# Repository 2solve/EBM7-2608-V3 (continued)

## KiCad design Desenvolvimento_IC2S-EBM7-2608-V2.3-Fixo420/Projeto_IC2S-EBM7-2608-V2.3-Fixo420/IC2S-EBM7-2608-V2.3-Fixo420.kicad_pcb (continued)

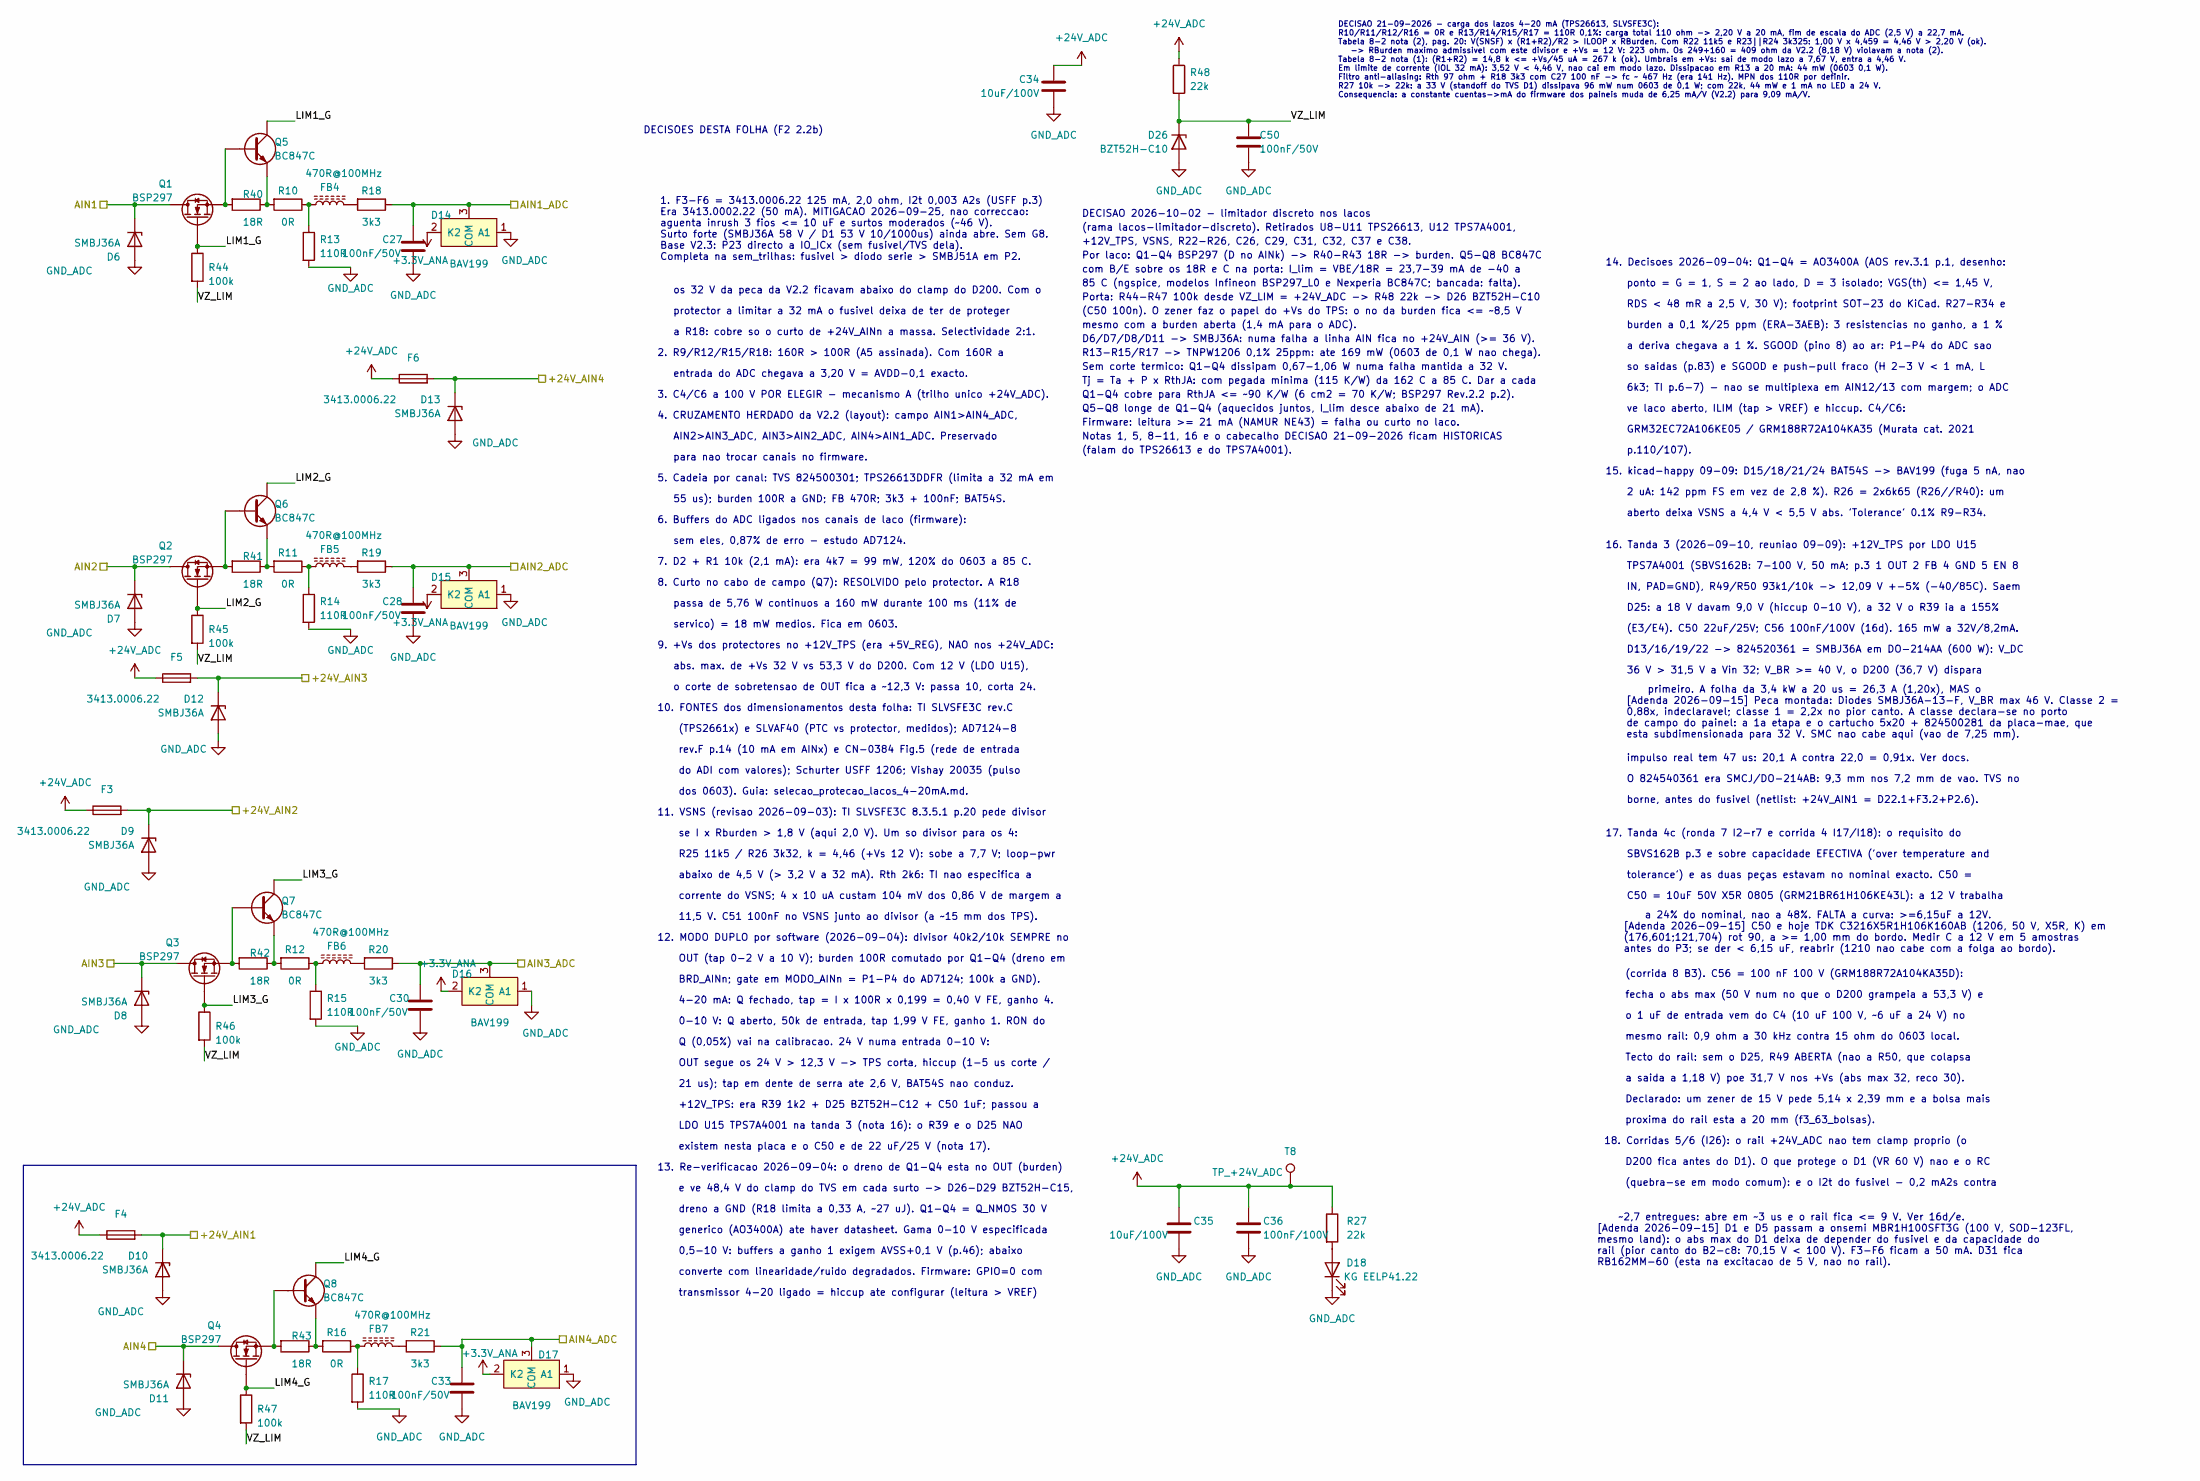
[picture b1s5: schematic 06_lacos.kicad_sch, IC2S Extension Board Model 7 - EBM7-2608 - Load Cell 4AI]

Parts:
C27, C28, C30, C33, C50: 100nF/50V; 0603C; MPN C1608X7R1H104K080AA
C34, C35: 10uF/100V; C_1210_3225Metric; MPN GRM32EC72A106ME05L
C36: 100nF/100V; 0603C; MPN GRM188R72A104KA35D
D6, D7, D8, D9, D10, D11, D12, D13: SMBJ36A; DO-214AA; MPN SMBJ36A-13-F
D14, D15, D16, D17: BAV199; SOT23-3; MPN BAV199LT1G
D18: KG EELP41.22; 0603LED; MPN KG EELP41.22-PHRH-35-A8J8-20-R18
D26: BZT52H-C10; SOD-123F; MPN BZT52H-C10,115
F3, F4, F5, F6: 3413.0006.22; 1206F; MPN 3413.0006.22
FB4, FB5, FB6, FB7: 470R@100MHz; 0603FB; MPN BLM18PG471SN1D
Q1, Q2, Q3, Q4: BSP297; SOT-223-3_TabPin2; MPN BSP297H6327XTSA1
Q5, Q6, Q7, Q8: BC847C; SOT-23; MPN BC847C,215
R10, R11, R12, R16: 0R; 0603R; Tolerance 0.1%; MPN RC0603JR-070RL
R13, R14, R15, R17: 110R; 1206R; Tolerance 0.1%; MPN TNPW1206110RBEEA
R18, R19, R20, R21: 3k3; 0603R; MPN RC0603FR-073K3L
R27: 22k; 0603R; MPN ERJ-3EKF2202V
R40, R41, R42, R43: 18R; 0603R; Tolerance 1%; MPN RC0603FR-0718RL
R44, R45, R46, R47: 100k; 0603R; Tolerance 1%; MPN RC0603FR-07100KL
R48: 22k; 0603R; Tolerance 1%; MPN RC0603FR-0722KL
T8: TP_+24V_ADC; TestPad_Via

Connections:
+3.3V_ANA: D14.2 (K2), D15.2 (K2), D16.2 (K2), D17.2 (K2); also elsewhere on the board
+24V_ADC: C34.1, C35.1, C36.1, F3.1, F4.1, F5.1, F6.1, R27.1, R48.1, T8.1 (1_1); also elsewhere on the board
/1 Conectores/+24V_AIN1: D10.1 (K), F4.2; also elsewhere on the board
/1 Conectores/+24V_AIN2: D9.1 (K), F3.2; also elsewhere on the board
/1 Conectores/+24V_AIN3: D12.1 (K), F5.2; also elsewhere on the board
/1 Conectores/+24V_AIN4: D13.1 (K), F6.2; also elsewhere on the board
/1 Conectores/AIN1: D6.1 (K), Q1.2 (D); also elsewhere on the board
/1 Conectores/AIN2: D7.1 (K), Q2.2 (D); also elsewhere on the board
/1 Conectores/AIN3: D8.1 (K), Q3.2 (D); also elsewhere on the board
/1 Conectores/AIN4: D11.1 (K), Q4.2 (D); also elsewhere on the board
/5 ADC/AIN1_ADC: C27.2, D14.3 (COM), R18.1; also elsewhere on the board
/5 ADC/AIN2_ADC: C28.2, D15.3 (COM), R19.1; also elsewhere on the board
/5 ADC/AIN3_ADC: C30.2, D16.3 (COM), R20.1; also elsewhere on the board
/5 ADC/AIN4_ADC: C33.2, D17.3 (COM), R21.1; also elsewhere on the board
/6 Lacos 4-20mA/LIM1_G: Q1.1 (G), Q5.3 (C), R44.1
/6 Lacos 4-20mA/LIM2_G: Q2.1 (G), Q6.3 (C), R45.1
/6 Lacos 4-20mA/LIM3_G: Q3.1 (G), Q7.3 (C), R46.1
/6 Lacos 4-20mA/LIM4_G: Q4.1 (G), Q8.3 (C), R47.1
/6 Lacos 4-20mA/VZ_LIM: C50.1, D26.1 (K), R44.2, R45.2, R46.2, R47.2, R48.2
GND_ADC: C27.1, C28.1, C30.1, C33.1, C34.2, C35.2, C36.2, C50.2, D6.2 (A), D7.2 (A), D8.2 (A), D9.2 (A), D10.2 (A), D11.2 (A), D12.2 (A), D13.2 (A), D14.1 (A1), D15.1 (A1), D16.1 (A1), D17.1 (A1), D18.1 (K), D26.2 (A), R13.2, R14.2, R15.2, R17.2; also elsewhere on the board
unnamed: D18.2 (A), R27.2
unnamed: FB4.1, R10.1, R13.1
unnamed: FB4.2, R18.2
unnamed: FB5.1, R11.1, R14.1
unnamed: FB5.2, R19.2
unnamed: FB6.1, R12.1, R15.1
unnamed: FB6.2, R20.2
unnamed: FB7.1, R16.1, R17.1
unnamed: FB7.2, R21.2
unnamed: Q1.3 (S), Q5.1 (B), R40.2
unnamed: Q2.3 (S), Q6.1 (B), R41.2
unnamed: Q3.3 (S), Q7.1 (B), R42.2
unnamed: Q4.3 (S), Q8.1 (B), R43.2
unnamed: Q5.2 (E), R10.2, R40.1
unnamed: Q6.2 (E), R11.2, R41.1
unnamed: Q7.2 (E), R12.2, R42.1
unnamed: Q8.2 (E), R16.2, R43.1

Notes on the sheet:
o 1 uF de entrada vem do C4 (10 uF 100 V, ~6 uF a 24 V) no
p.110/107).
BRD_AINn; gate em MODO_AINn = P1-P4 do AD7124; 100k a GND).
9. +Vs dos protectores no +12V_TPS (era +5V_REG), NAO nos +24V_ADC:
18. Corridas 5/6 (I26): o rail +24V_ADC nao tem clamp proprio (o
(quebra-se em modo comum): e o I2t do fusivel - 0,2 mA2s contra
o corte de sobretensao de OUT fica a ~12,3 V: passa 10, corta 24.
55 us); burden 100R a GND; FB 470R; 3k3 + 100nF; BAT54S.
Tecto do rail: sem o D25, R49 ABERTA (nao a R50, que colapsa
~2,7 entregues: abre em ~3 us e o rail fica <= 9 V. Ver 16d/e. [Adenda 2026-09-15] D1 e D5 passam a onsemi MBR1H100SFT3G (100 V, SOD-123FL, mesmo land): o abs max do D1 deixa de depender do fusivel e da capacidade do rail (pior canto do B2-c8: 70,15 V < 100 V). F3-F6 ficam a 50 mA. D31 fica RB162MM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
17. Tanda 4c (ronda 7 I2-r7 e corrida 4 I17/I18): o requisito do
ponto = G = 1, S = 2 ao lado, D = 3 isolado; VGS(th) <= 1,45 V,
D200 fica antes do D1). O que protege o D1 (VR 60 V) nao e o RC
(E3/E4). C50 22uF/25V; C56 100nF/100V (16d). 165 mW a 32V/8,2mA.
4-20 mA: Q fechado, tap = I x 100R x 0,199 = 0,40 V FE, ganho 4.
rev.F p.14 (10 mA em AINx) e CN-0384 Fig.5 (rede de entrada
15. kicad-happy 09-09: D15/18/21/24 BAT54S -> BAV199 (fuga 5 nA, nao
AIN2>AIN3_ADC, AIN3>AIN2_ADC, AIN4>AIN1_ADC. Preservado
dreno a GND (R18 limita a 0,33 A, ~27 uJ). Q1-Q4 = Q_NMOS 30 V
passa de 5,76 W continuos a 160 mW durante 100 ms (11% de
14. Decisoes 2026-09-04: Q1-Q4 = AO3400A (AOS rev.3.1 p.1, desenho:
DECISOES DESTA FOLHA (F2 2.2b)
7. D2 + R1 10k (2,1 mA): era 4k7 = 99 mW, 120% do 0603 a 85 C.
abaixo de 4,5 V (> 3,2 V a 32 mA). Rth 2k6: TI nao especifica a
4. CRUZAMENTO HERDADO da V2.2 (layout): campo AIN1>AIN4_ADC,
(corrida 8 B3). C56 = 100 nF 100 V (GRM188R72A104KA35D):
protector a limitar a 32 mA o fusivel deixa de ter de proteger
burden a 0,1 %/25 ppm (ERA-3AEB): 3 resistencias no ganho, a 1 %
mesmo rail: 0,9 ohm a 30 kHz contra 15 ohm do 0603 local.
borne, antes do fusivel (netlist: +24V_AIN1 = D22.1+F3.2+P2.6).
(TPS2661x) e SLVAF40 (PTC vs protector, medidos); AD7124-8
R25 11k5 / R26 3k32, k = 4,46 (+Vs 12 V): sobe a 7,7 V; loop-pwr
OUT segue os 24 V > 12,3 V -> TPS corta, hiccup (1-5 us corte /
5. Cadeia por canal: TVS 824500301; TPS26613DDFR (limita a 32 mA em
generico (AO3400A) ate haver datasheet. Gama 0-10 V especificada
10. FONTES dos dimensionamentos desta folha: TI SLVSFE3C rev.C
servico) = 18 mW medios. Fica em 0603.
1. F3-F6 = 3413.0006.22 125 mA, 2,0 ohm, I2t 0,003 A2s (USFF p.3) Era 3413.0002.22 (50 mA). MITIGACAO 2026-09-25, nao correccao: aguenta inrush 3 fios <= 10 uF e surtos moderados (~46 V). Surto forte (SMBJ36A 58 V / D1 53 V 10/1000us) ainda abre. Sem G8. Base V2.3: P23 directo a IO_ICx (sem fusivel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
LDO U15 TPS7A4001 na tanda 3 (nota 16): o R39 e o D25 NAO
0-10 V: Q aberto, 50k de entrada, tap 1,99 V FE, ganho 1. RON do

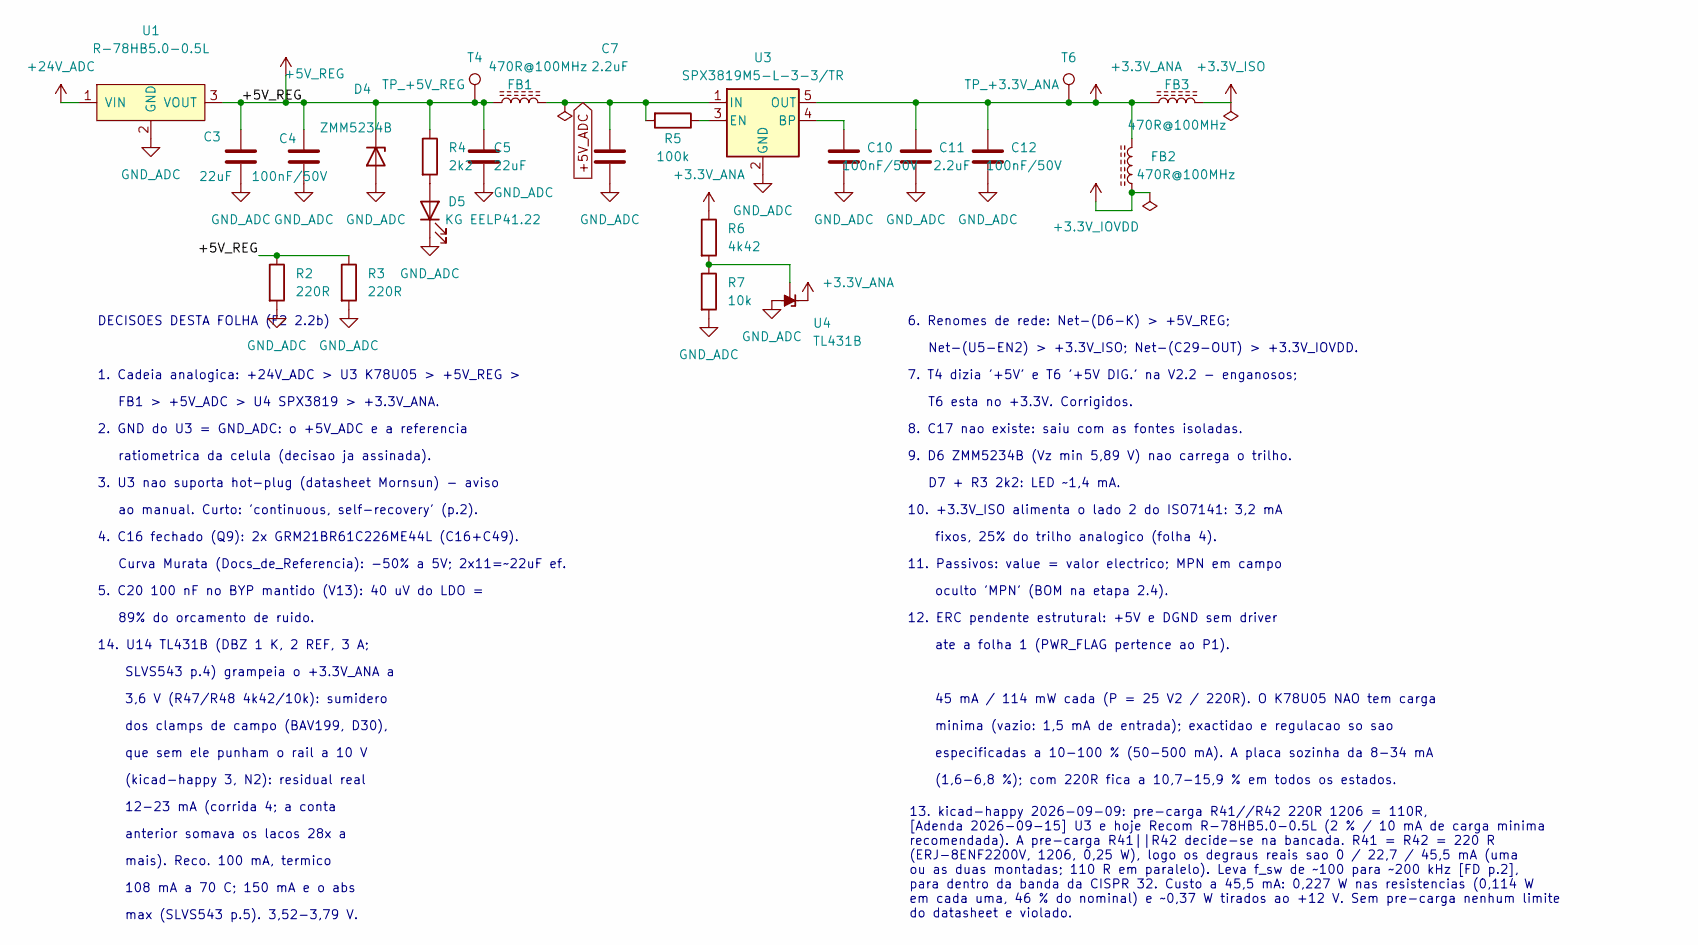
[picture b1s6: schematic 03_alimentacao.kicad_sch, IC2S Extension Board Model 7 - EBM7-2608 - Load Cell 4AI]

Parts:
C3, C5: 22uF; C_0805_2012Metric; MPN CL21A226KOQNNNG
C4, C10, C12: 100nF/50V; 0603C; MPN C1608X7R1H104K080AA
C7, C11: 2.2uF; 0603C; MPN C1608X5R1E225K080AB
D4: ZMM5234B; SOD-80C; MPN ZMM5234B
D5: KG EELP41.22; 0603LED; MPN KG EELP41.22-PHRH-35-A8J8-20-R18
FB1, FB2, FB3: 470R@100MHz; 0603FB; MPN BLM18PG471SN1D
R2, R3: 220R; 1206R; MPN RC1206FR-07220RL
R4: 2k2; 0603R; MPN RC0603FR-072K2L
R5: 100k; 0603R; MPN CRCW0603100KFKEA
R6: 4k42; 0603R; MPN RMCF0603FT4K42
R7: 10k; 0603R; MPN RC0603FR-0710KL
T4: TP_+5V_REG; TestPad_Via
T6: TP_+3.3V_ANA; TestPad_Via
U1: R-78HB5.0-0.5L; R-78HBxx-0.5L_SIP-3H; MPN R-78HB5.0-0.5L
U3: SPX3819M5-L-3-3/TR; SOT-23-5; MPN SPX3819M5-L-3-3/TR
U4: TL431B; SOT23-3; MPN TL431BQDBZR

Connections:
+3.3V_ANA: C11.2, C12.2, FB2.2, FB3.1, R6.1, T6.1 (1_1), U3.5 (OUT), U4.1 (K); also elsewhere on the board
+3.3V_IOVDD: FB2.1; also elsewhere on the board
+3.3V_ISO: FB3.2; also elsewhere on the board
+5V_ADC: C7.2, FB1.2, R5.2, U3.1 (IN); also elsewhere on the board
+5V_REG: C3.2, C4.2, C5.2, D4.1 (K), FB1.1, R2.1, R3.1, R4.1, T4.1 (1_1), U1.3 (VOUT)
+24V_ADC: U1.1 (VIN); also elsewhere on the board
GND_ADC: C3.1, C4.1, C5.1, C7.1, C10.1, C11.1, C12.1, D4.2 (A), D5.1 (K), R2.2, R3.2, R7.2, U1.2 (GND), U3.2 (GND), U4.3 (A); also elsewhere on the board
unnamed: D5.2 (A), R4.2
unnamed: C10.2, U3.4 (BP)
unnamed: R5.1, U3.3 (EN)
unnamed: R6.2, R7.1, U4.2 (REF)

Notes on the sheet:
dos clamps de campo (BAV199, D30),
mais). Reco. 100 mA, termico
ate a folha 1 (PWR_FLAG pertence ao P1).
8. C17 nao existe: saiu com as fontes isoladas.
minima (vazio: 1,5 mA de entrada); exactidao e regulacao so sao
7. T4 dizia '+5V' e T6 '+5V DIG.' na V2.2 - enganosos;
6. Renomes de rede: Net-(D6-K) > +5V_REG;
3. U3 nao suporta hot-plug (datasheet Mornsun) - aviso
3,6 V (R47/R48 4k42/10k): sumidero
ratiometrica da celula (decisao ja assinada).
D7 + R3 2k2: LED ~1,4 mA.
FB1 > +5V_ADC > U4 SPX3819 > +3.3V_ANA.
que sem ele punham o rail a 10 V
4. C16 fechado (Q9): 2x GRM21BR61C226ME44L (C16+C49).
108 mA a 70 C; 150 mA e o abs
14. U14 TL431B (DBZ 1 K, 2 REF, 3 A;
anterior somava os lacos 28x a
Curva Murata (Docs_de_Referencia): -50% a 5V; 2x11=~22uF ef.
10. +3.3V_ISO alimenta o lado 2 do ISO7141: 3,2 mA
T6 esta no +3.3V. Corrigidos.
oculto 'MPN' (BOM na etapa 2.4).
13. kicad-happy 2026-09-09: pre-carga R41//R42 220R 1206 = 110R, [Adenda 2026-09-15] U3 e hoje Recom R-78HB5.0-0.5L (2 % / 10 mA de carga minima recomendada). A pre-carga R41||R42 decide-se na bancada. R41 = R42 = 220 R (ERJ-8ENF2200V, 1206, 0,25 W), logo os degraus reais sao 0 / 22,7 / 45,5 mA (um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
11. Passivos: value = valor electrico; MPN em campo
12. ERC pendente estrutural: +5V e DGND sem driver
2. GND do U3 = GND_ADC: o +5V_ADC e a referencia
(1,6-6,8 %); com 220R fica a 10,7-15,9 % em todos os estados.
fixos, 25% do trilho analogico (folha 4).
5. C20 100 nF no BYP mantido (V13): 40 uV do LDO =
1. Cadeia analogica: +24V_ADC > U3 K78U05 > +5V_REG >
Net-(U5-EN2) > +3.3V_ISO; Net-(C29-OUT) > +3.3V_IOVDD.
DECISOES DESTA FOLHA (F2 2.2b)
SLVS543 p.4) grampeia o +3.3V_ANA a
(kicad-happy 3, N2): residual real
45 mA / 114 mW cada (P = 25 V2 / 220R). O K78U05 NAO tem carga
ao manual. Curto: 'continuous, self-recovery' (p.2).
9. D6 ZMM5234B (Vz min 5,89 V) nao carrega o trilho.
12-23 mA (corrida 4; a conta
especificadas a 10-100 % (50-500 mA). A placa sozinha da 8-34 mA
89% do orcamento de ruido.
max (SLVS543 p.5). 3,52-3,79 V.

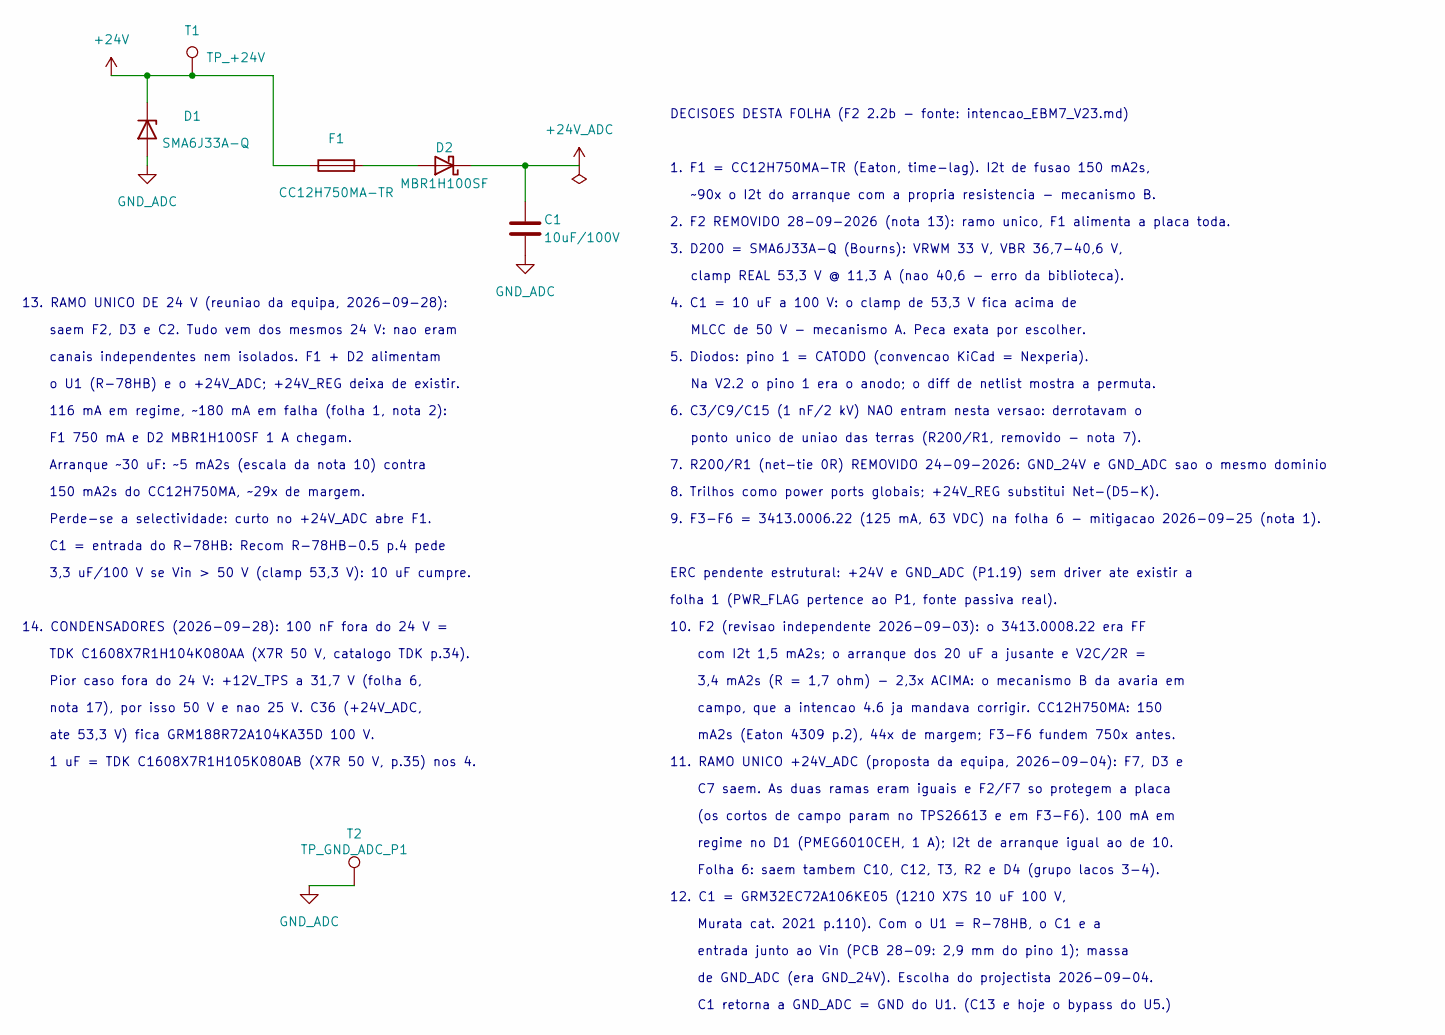
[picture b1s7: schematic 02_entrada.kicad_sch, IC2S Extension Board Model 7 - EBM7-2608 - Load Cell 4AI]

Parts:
C1: 10uF/100V; C_1210_3225Metric; MPN GRM32EC72A106ME05L
D1: SMA6J33A-Q; DO-214; MPN SMA6J33A-Q
D2: MBR1H100SF; SOD123; MPN MBR1H100SFT3G
F1: CC12H750MA-TR; 1206F; MPN CC12H750MA-TR
T1: TP_+24V; TestPad_Via
T2: TP_GND_ADC_P1; TestPad_Via

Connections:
+24V: D1.1 (K), F1.1, T1.1 (1_1); also elsewhere on the board
+24V_ADC: C1.1, D2.1 (K); also elsewhere on the board
GND_ADC: C1.2, D1.2 (A), T2.1 (1_1); also elsewhere on the board
unnamed: D2.2 (A), F1.2

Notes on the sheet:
8. Trilhos como power ports globais; +24V_REG substitui Net-(D5-K).
13. RAMO UNICO DE 24 V (reuniao da equipa, 2026-09-28):
Pior caso fora do 24 V: +12V_TPS a 31,7 V (folha 6,
Murata cat. 2021 p.110). Com o U1 = R-78HB, o C1 e a
5. Diodos: pino 1 = CATODO (convencao KiCad = Nexperia).
Folha 6: saem tambem C10, C12, T3, R2 e D4 (grupo lacos 3-4).
~90x o I2t do arranque com a propria resistencia - mecanismo B.
Arranque ~30 uF: ~5 mA2s (escala da nota 10) contra
F1 750 mA e D2 MBR1H100SF 1 A chegam.
Perde-se a selectividade: curto no +24V_ADC abre F1.
MLCC de 50 V - mecanismo A. Peca exata por escolher.
12. C1 = GRM32EC72A106KE05 (1210 X7S 10 uF 100 V,
7. R200/R1 (net-tie 0R) REMOVIDO 24-09-2026: GND_24V e GND_ADC sao o mesmo dominio
com I2t 1,5 mA2s; o arranque dos 20 uF a jusante e V2C/2R =
1 uF = TDK C1608X7R1H105K080AB (X7R 50 V, p.35) nos 4.
150 mA2s do CC12H750MA, ~29x de margem.
4. C1 = 10 uF a 100 V: o clamp de 53,3 V fica acima de
6. C3/C9/C15 (1 nF/2 kV) NAO entram nesta versao: derrotavam o
C1 retorna a GND_ADC = GND do U1. (C13 e hoje o bypass do U5.)
TDK C1608X7R1H104K080AA (X7R 50 V, catalogo TDK p.34).
de GND_ADC (era GND_24V). Escolha do projectista 2026-09-04.
10. F2 (revisao independente 2026-09-03): o 3413.0008.22 era FF
saem F2, D3 e C2. Tudo vem dos mesmos 24 V: nao eram
116 mA em regime, ~180 mA em falha (folha 1, nota 2):
ponto unico de uniao das terras (R200/R1, removido - nota 7).
9. F3-F6 = 3413.0006.22 (125 mA, 63 VDC) na folha 6 - mitigacao 2026-09-25 (nota 1).
folha 1 (PWR_FLAG pertence ao P1, fonte passiva real).
campo, que a intencao 4.6 ja mandava corrigir. CC12H750MA: 150
nota 17), por isso 50 V e nao 25 V. C36 (+24V_ADC,
3. D200 = SMA6J33A-Q (Bourns): VRWM 33 V, VBR 36,7-40,6 V,
clamp REAL 53,3 V @ 11,3 A (nao 40,6 - erro da biblioteca).
ate 53,3 V) fica GRM188R72A104KA35D 100 V.
o U1 (R-78HB) e o +24V_ADC; +24V_REG deixa de existir.
entrada junto ao Vin (PCB 28-09: 2,9 mm do pino 1); massa
14. CONDENSADORES (2026-09-28): 100 nF fora do 24 V =
canais independentes nem isolados. F1 + D2 alimentam
1. F1 = CC12H750MA-TR (Eaton, time-lag). I2t de fusao 150 mA2s,
mA2s (Eaton 4309 p.2), 44x de margem; F3-F6 fundem 750x antes.
ERC pendente estrutural: +24V e GND_ADC (P1.19) sem driver ate existir a
2. F2 REMOVIDO 28-09-2026 (nota 13): ramo unico, F1 alimenta a placa toda.

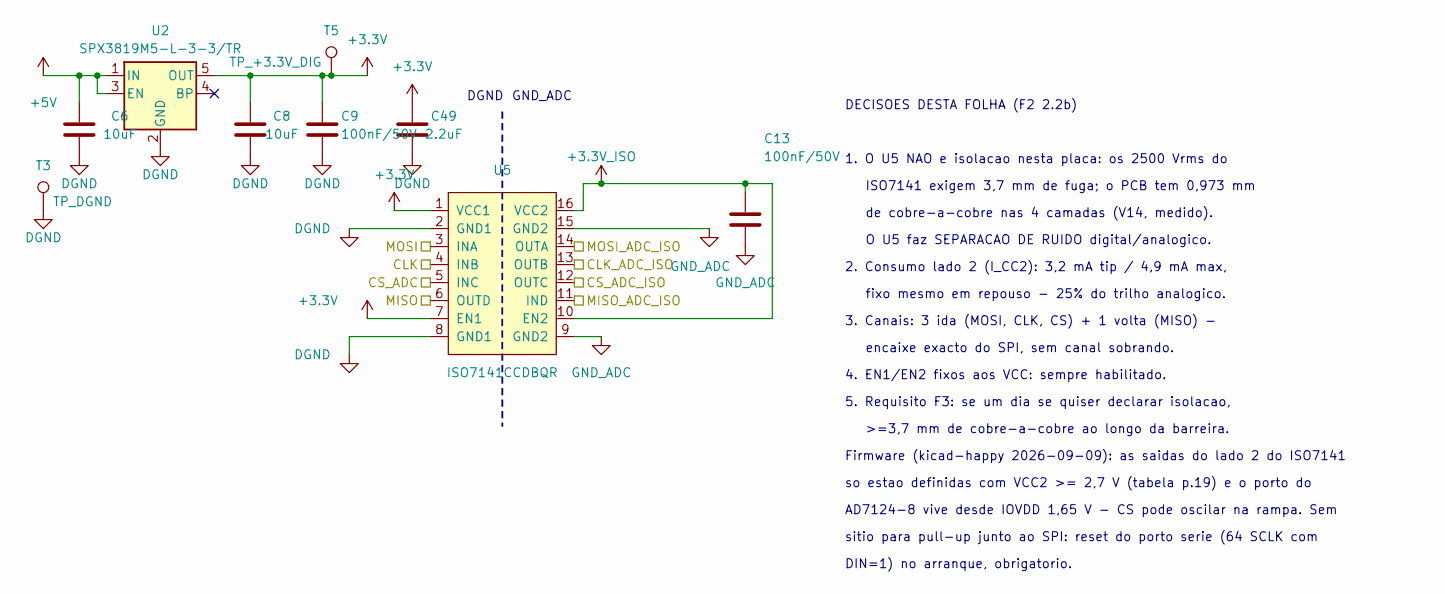
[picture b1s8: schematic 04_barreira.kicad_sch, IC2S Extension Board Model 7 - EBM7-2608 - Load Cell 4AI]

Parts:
C6, C8: 10uF; 0603C; MPN 0603YD106KAT2A
C9, C13: 100nF/50V; 0603C; MPN C1608X7R1H104K080AA
C49: 2.2uF; 0603C; MPN C1608X5R1E225K080AB
T3: TP_DGND; TestPad_Via
T5: TP_+3.3V_DIG; TestPad_Via
U2: SPX3819M5-L-3-3/TR; SOT-23-5; MPN SPX3819M5-L-3-3/TR
U5: ISO7141CCDBQR; SSOP16-4.9x3.9mm; MPN ISO7141CCDBQR

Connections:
+3.3V: C8.2, C9.1, C49.2, T5.1 (1_1), U2.5 (OUT), U5.1 (VCC1), U5.7 (EN1)
+3.3V_ISO: C13.1, U5.10 (EN2), U5.16 (VCC2); also elsewhere on the board
+5V: C6.2, U2.1 (IN), U2.3 (EN); also elsewhere on the board
/4 Barreira digital/CLK_ADC_ISO: U5.13 (OUTB); also elsewhere on the board
/4 Barreira digital/CS_ADC_ISO: U5.12 (OUTC); also elsewhere on the board
/4 Barreira digital/MISO_ADC_ISO: U5.11 (IND); also elsewhere on the board
/4 Barreira digital/MOSI_ADC_ISO: U5.14 (OUTA); also elsewhere on the board
/CLK: U5.4 (INB); also elsewhere on the board
/CS_ADC: U5.5 (INC); also elsewhere on the board
/MISO: U5.6 (OUTD); also elsewhere on the board
/MOSI: U5.3 (INA); also elsewhere on the board
DGND: C6.1, C8.1, C9.2, C49.1, T3.1 (1_1), U2.2 (GND), U5.2 (GND1), U5.8 (GND1); also elsewhere on the board
GND_ADC: C13.2, U5.9 (GND2), U5.15 (GND2); also elsewhere on the board

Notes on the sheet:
AD7124-8 vive desde IOVDD 1,65 V - CS pode oscilar na rampa. Sem
DECISOES DESTA FOLHA (F2 2.2b)
ISO7141 exigem 3,7 mm de fuga; o PCB tem 0,973 mm
sitio para pull-up junto ao SPI: reset do porto serie (64 SCLK com
encaixe exacto do SPI, sem canal sobrando.
de cobre-a-cobre nas 4 camadas (V14, medido).
5. Requisito F3: se um dia se quiser declarar isolacao,
2. Consumo lado 2 (I_CC2): 3,2 mA tip / 4,9 mA max,
DGND
Firmware (kicad-happy 2026-09-09): as saidas do lado 2 do ISO7141
1. O U5 NAO e isolacao nesta placa: os 2500 Vrms do
O U5 faz SEPARACAO DE RUIDO digital/analogico.
GND_ADC
4. EN1/EN2 fixos aos VCC: sempre habilitado.
3. Canais: 3 ida (MOSI, CLK, CS) + 1 volta (MISO) -
so estao definidas com VCC2 >= 2,7 V (tabela p.19) e o porto do
fixo mesmo em repouso - 25% do trilho analogico.
>=3,7 mm de cobre-a-cobre ao longo da barreira.
DIN=1) no arranque, obrigatorio.

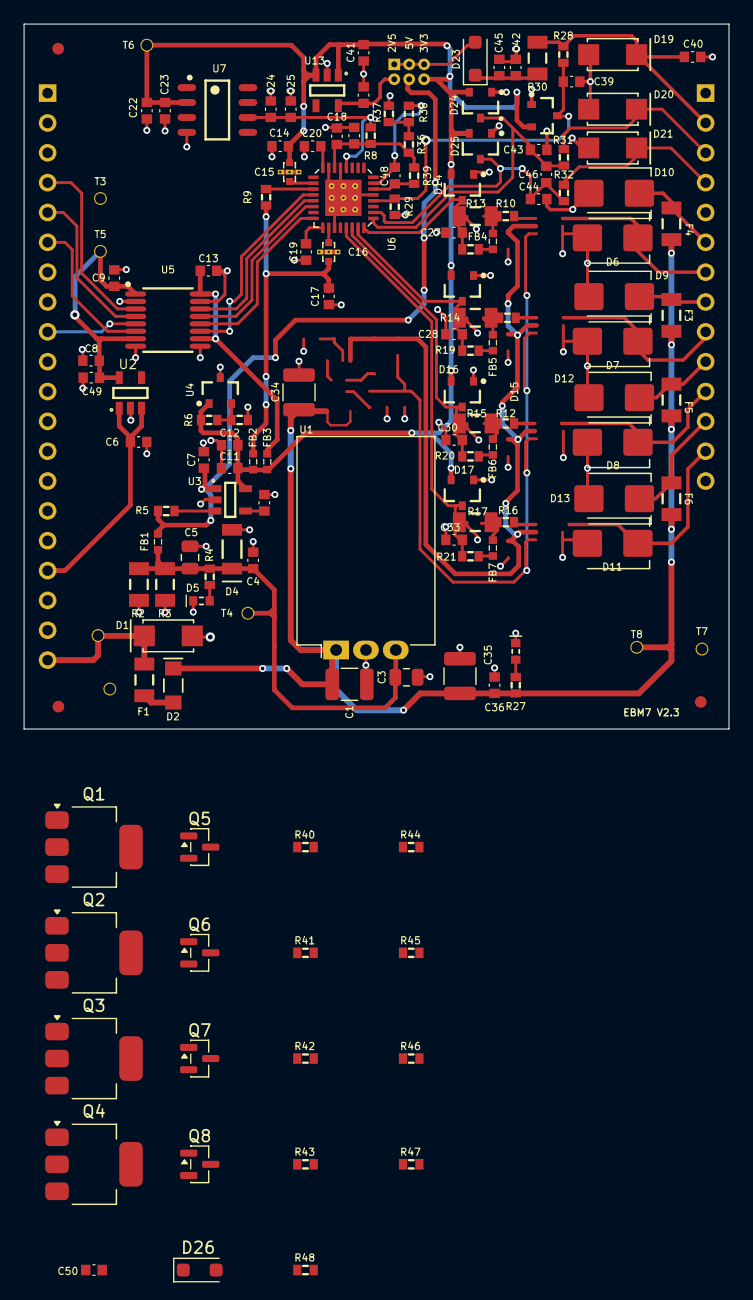
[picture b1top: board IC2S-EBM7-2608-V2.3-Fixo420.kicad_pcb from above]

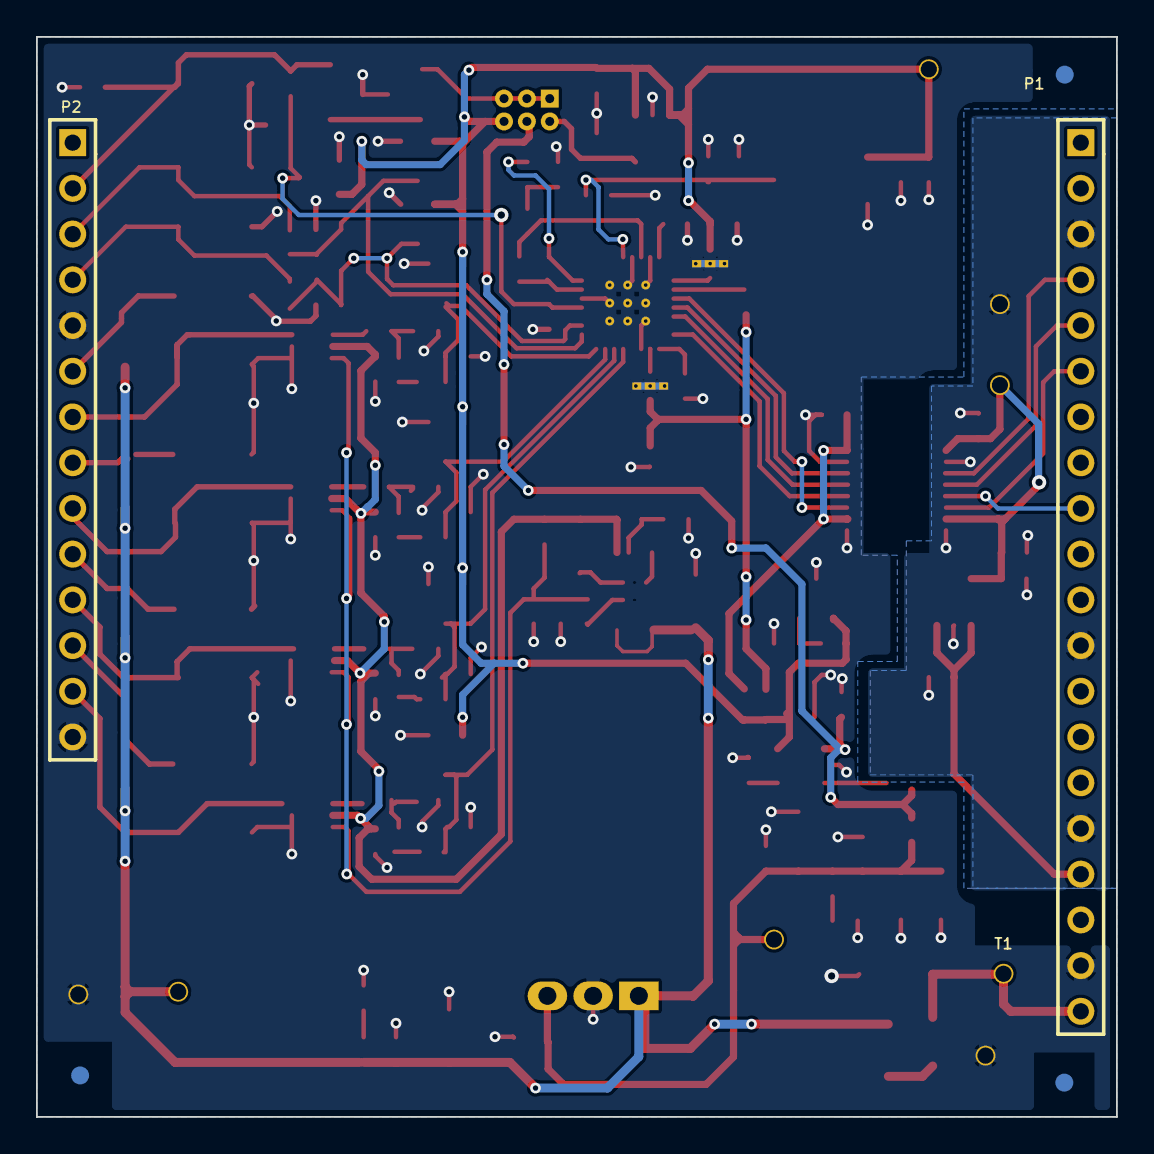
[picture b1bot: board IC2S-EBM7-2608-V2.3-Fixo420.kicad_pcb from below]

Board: 4 copper layers, 60.0 x 60.0 mm, 149 parts (4 on the bottom side), 77 nets.
